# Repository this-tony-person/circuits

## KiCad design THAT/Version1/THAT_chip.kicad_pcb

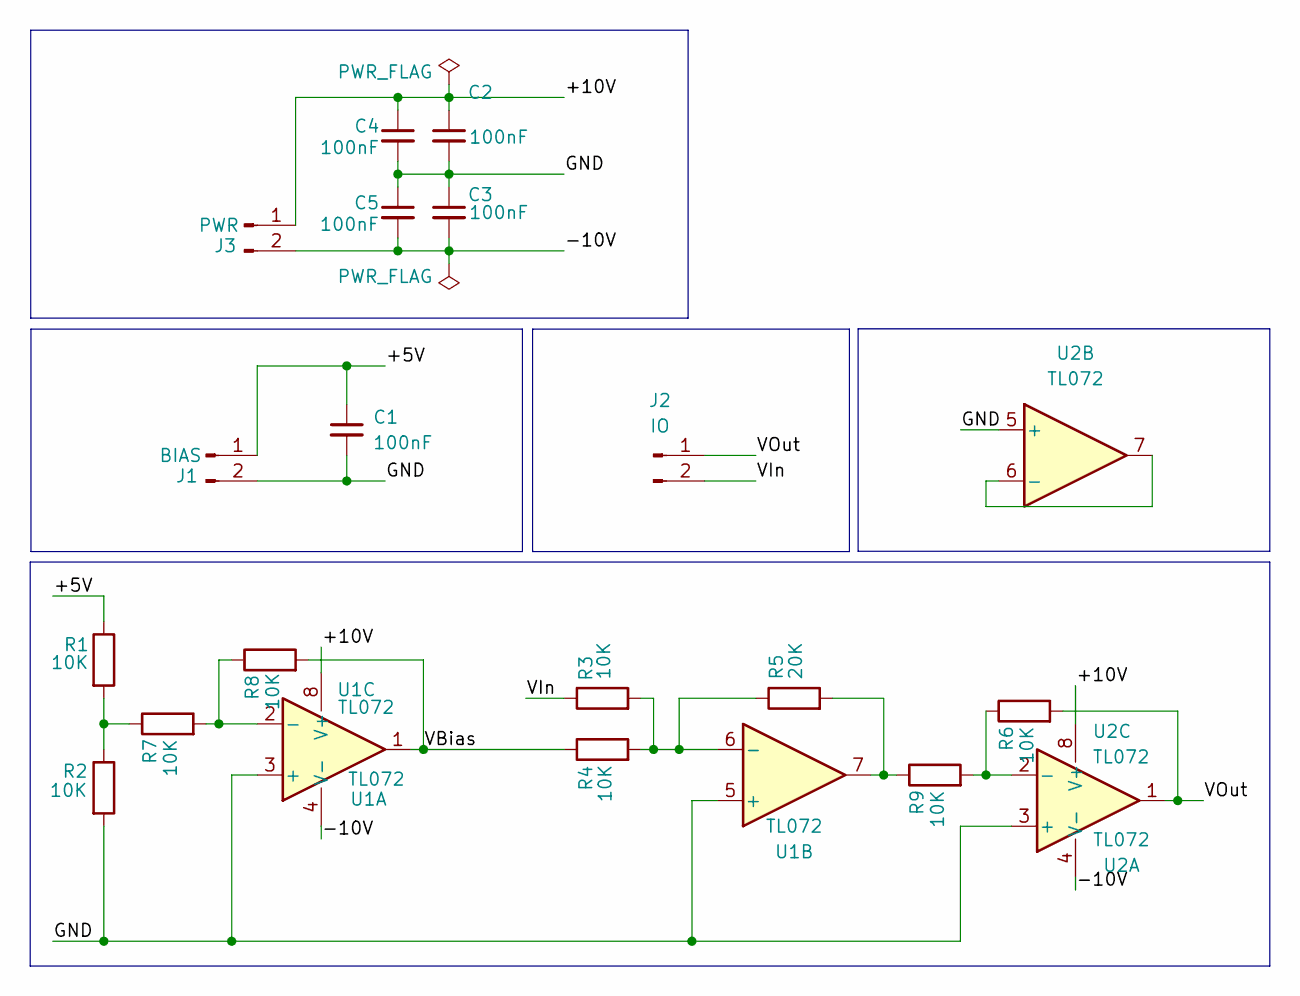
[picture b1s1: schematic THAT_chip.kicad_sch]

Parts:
C1, C2, C3, C4, C5: 100nF; C_Disc_D5.1mm_W3.2mm_P5.00mm
J1: BIAS; PinHeader_1x02_P2.54mm_Vertical
J2: IO; PinHeader_1x02_P2.54mm_Vertical
J3: PWR; PinHeader_1x02_P2.54mm_Vertical
R1, R2, R3, R4, R6, R7, R8, R9: 10K; R_Axial_DIN0207_L6.3mm_D2.5mm_P7.62mm_Horizontal
R5: 20K; R_Axial_DIN0207_L6.3mm_D2.5mm_P7.62mm_Horizontal
U1, U2: TL072

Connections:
/+5V: C1.1, J1.1, R1.1
/+10V: C2.1, C4.1, J3.1, U1.8 (V+), U2.8 (V+)
/-10V: C3.2, C5.2, J3.2, U1.4 (V-), U2.4 (V-)
/GND: C1.2, C2.2, C3.1, C4.2, C5.1, J1.2, R2.2, U1.3 (+), U1.5 (+), U2.3 (+), U2.5 (+)
/VBias: R4.1, R8.2, U1.1
/VIn: J2.2, R3.1
/VOut: J2.1, R6.2, U2.1
unnamed: R1.2, R2.1, R7.1
unnamed: R5.2, R9.1, U1.7
unnamed: R7.2, R8.1, U1.2 (-)
unnamed: R3.2, R4.2, R5.1, U1.6 (-)
unnamed: R6.1, R9.2, U2.2 (-)
unnamed: U2.6 (-), U2.7

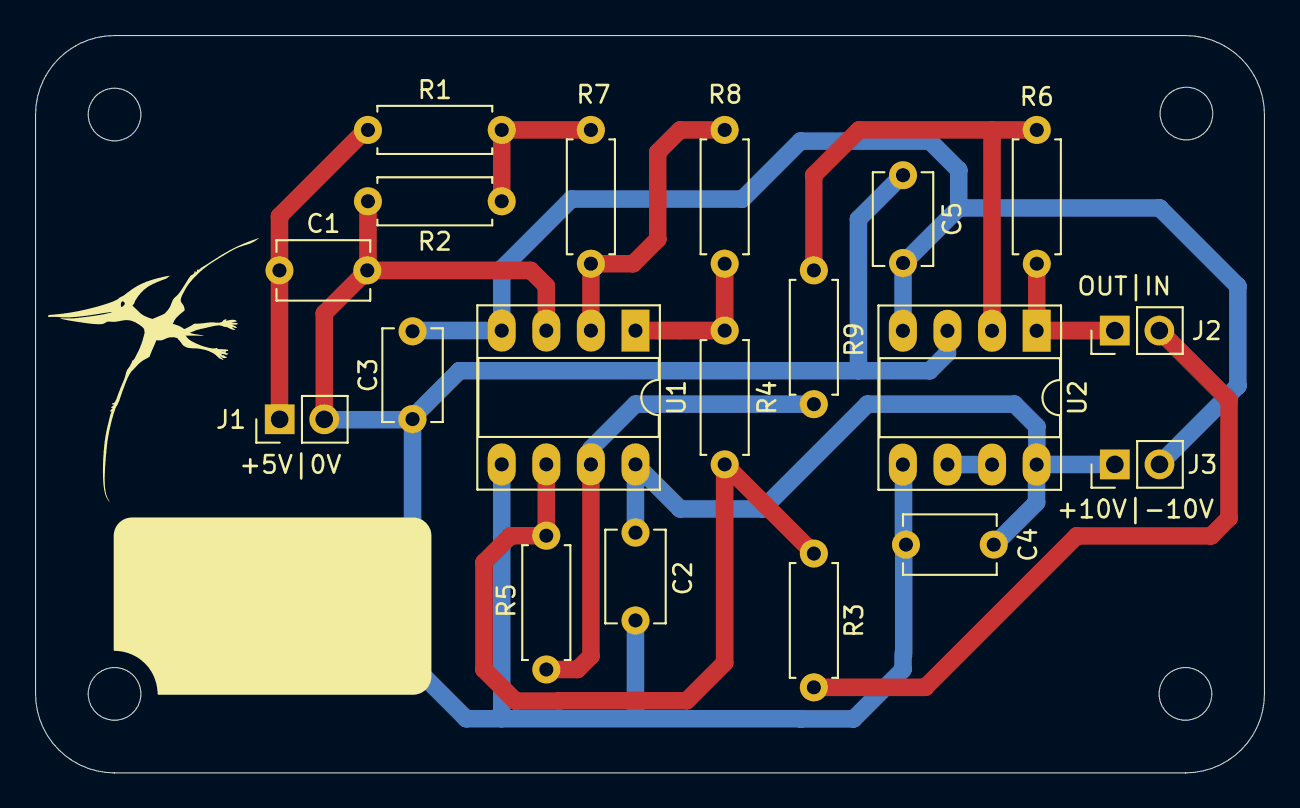
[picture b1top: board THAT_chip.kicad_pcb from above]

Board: 2 copper layers, 70.0 x 42.0 mm, 19 parts (0 on the bottom side), 13 nets.

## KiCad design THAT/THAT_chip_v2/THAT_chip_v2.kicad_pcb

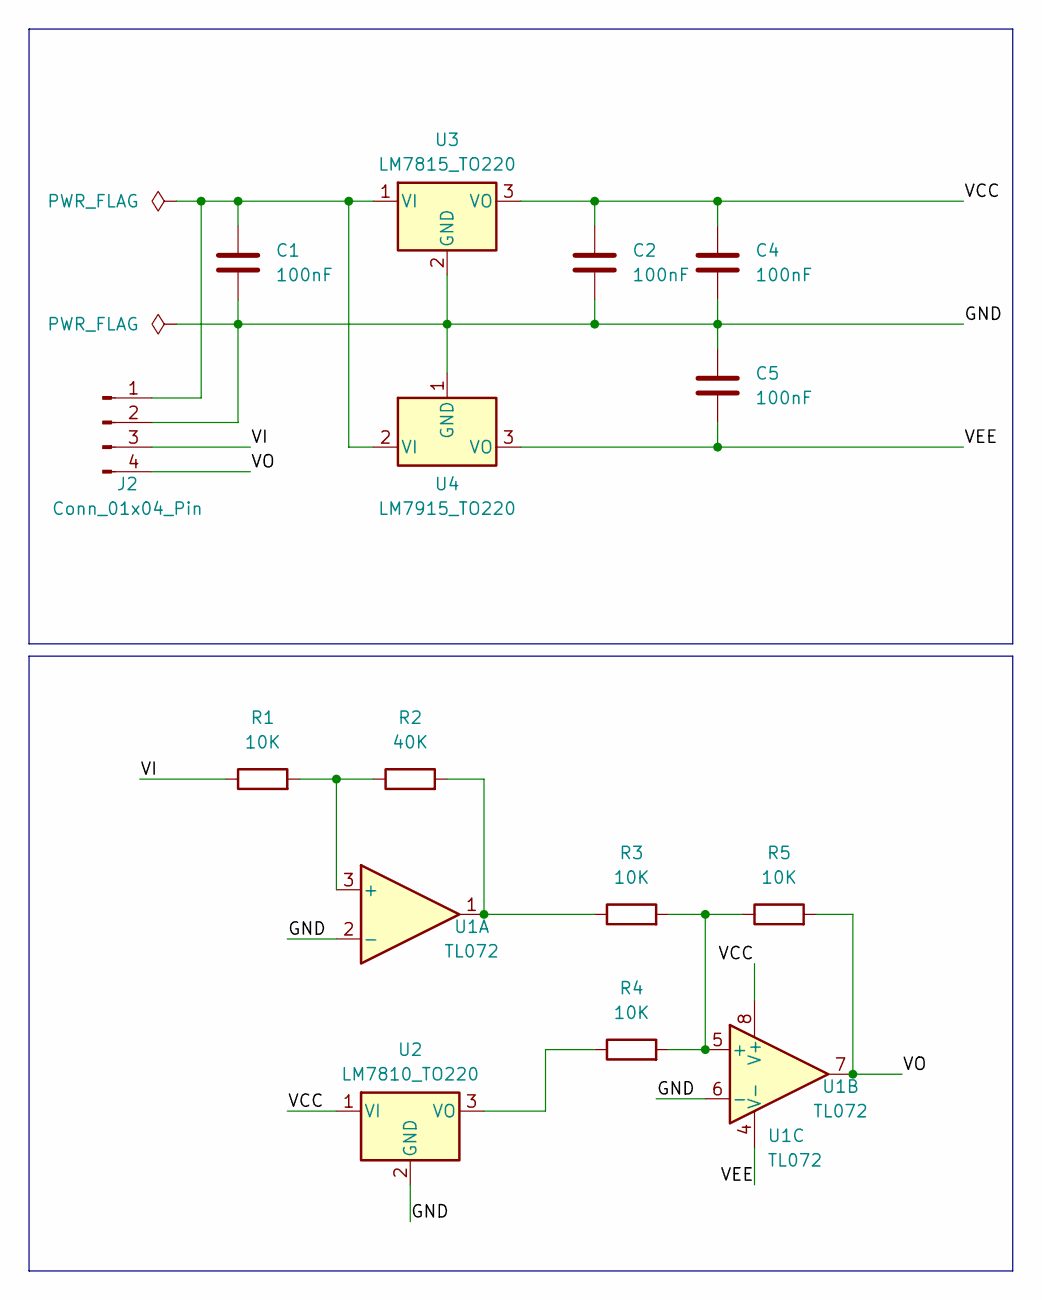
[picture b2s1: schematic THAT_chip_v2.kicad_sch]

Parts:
C1, C2, C4, C5: 100nF; C_Disc_D5.1mm_W3.2mm_P5.00mm
J2: Conn_01x04_Pin; PinHeader_1x04_P2.54mm_Vertical
R1, R3, R4, R5: 10K; R_Axial_DIN0207_L6.3mm_D2.5mm_P7.62mm_Horizontal
R2: 40K; R_Axial_DIN0207_L6.3mm_D2.5mm_P7.62mm_Horizontal
U1: TL072; DIP-8_W7.62mm_Socket_LongPads
U2: LM7810_TO220; TO-220-3_Vertical
U3: LM7815_TO220; TO-220-3_Vertical
U4: LM7915_TO220; TO-220-3_Vertical

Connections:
/GND: C1.2, C2.2, C4.2, C5.1, J2.2, U1.2 (-), U1.6 (-), U2.2 (GND), U3.2 (GND), U4.1 (GND)
/VCC: C2.1, C4.1, U1.8 (V+), U2.1 (VI), U3.3 (VO)
/VEE: C5.2, U1.4 (V-), U4.3 (VO)
/VI: J2.3, R1.1
/VO: J2.4, R5.2, U1.7
unnamed: C1.1, J2.1, U3.1 (VI), U4.2 (VI)
unnamed: R2.2, R3.1, U1.1
unnamed: R1.2, R2.1, U1.3 (+)
unnamed: R3.2, R4.2, R5.1, U1.5 (+)
unnamed: R4.1, U2.3 (VO)

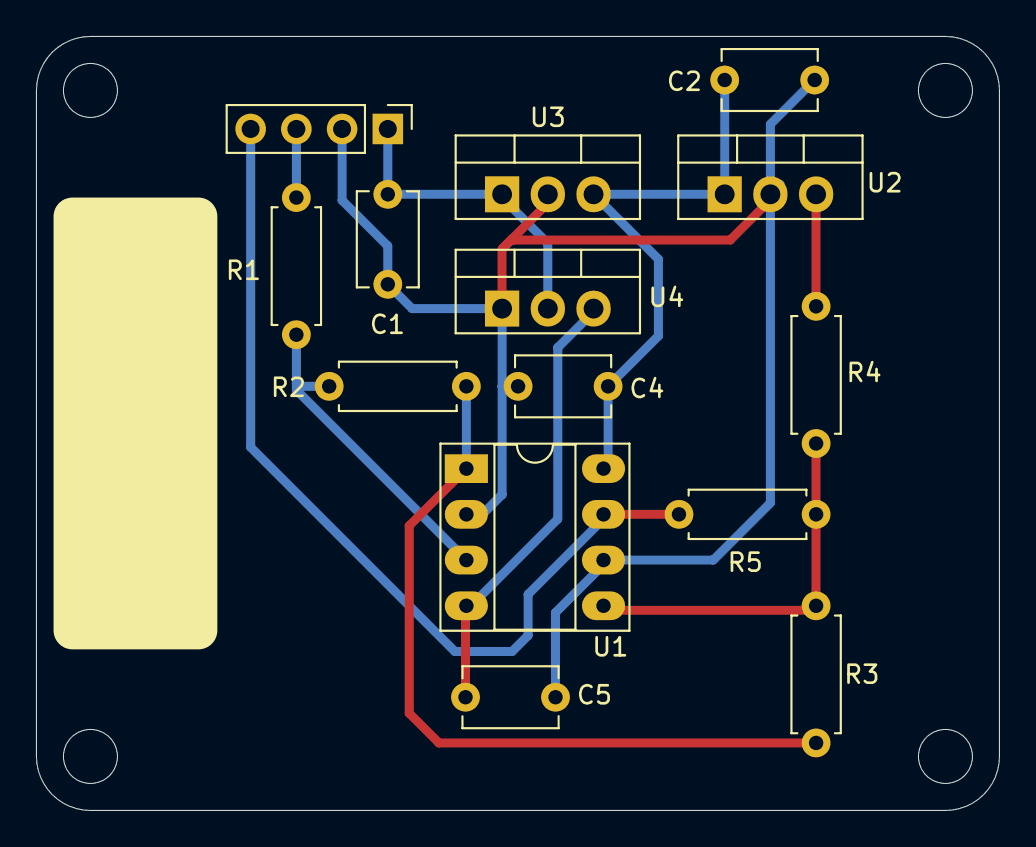
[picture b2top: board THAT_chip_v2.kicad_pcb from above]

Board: 2 copper layers, 53.5 x 43.0 mm, 14 parts (0 on the bottom side), 10 nets.

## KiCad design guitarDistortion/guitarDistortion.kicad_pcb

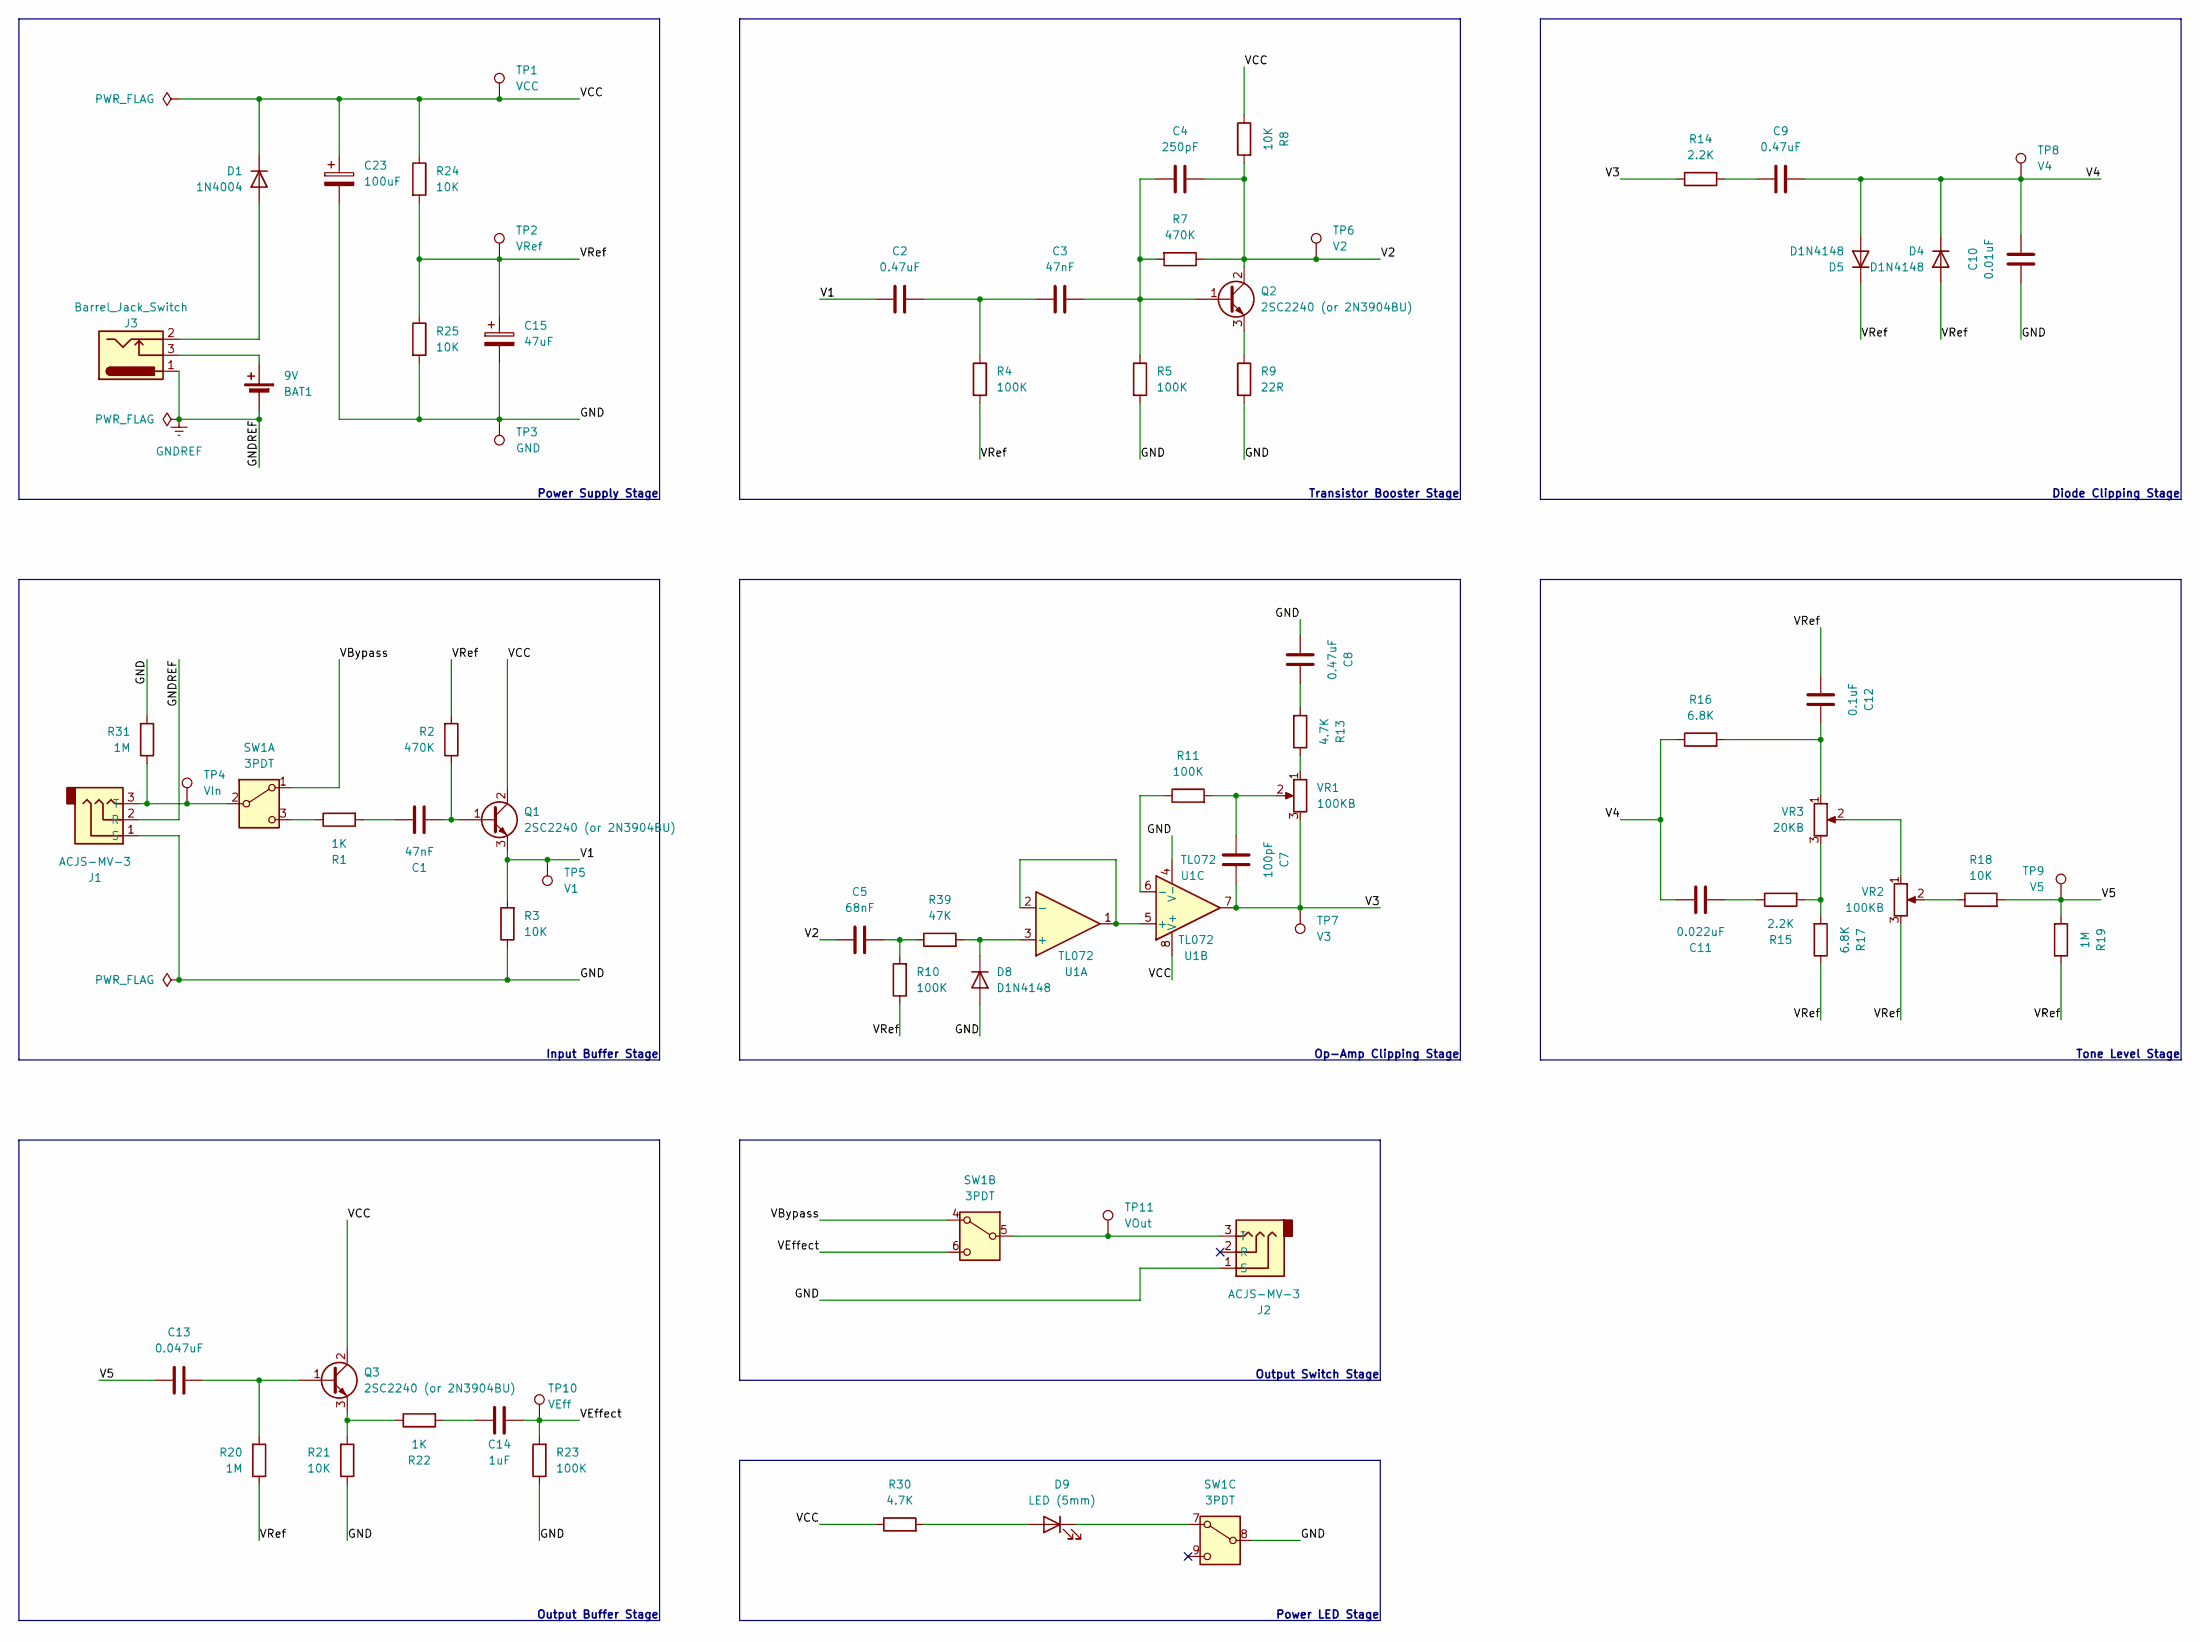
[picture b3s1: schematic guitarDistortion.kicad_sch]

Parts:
BAT1: 9V; JST_PH_B2B-PH-K_1x02_P2.00mm_Vertical
C1, C3: 47nF; C_Disc_D5.1mm_W3.2mm_P2.54mm
C2, C8, C9: 0.47uF; C_Disc_D5.1mm_W3.2mm_P2.54mm
C4: 250pF; C_Disc_D5.1mm_W3.2mm_P2.54mm
C5: 68nF; C_Disc_D5.1mm_W3.2mm_P2.54mm
C7: 100pF; C_Disc_D5.1mm_W3.2mm_P2.54mm
C10: 0.01uF; C_Disc_D5.1mm_W3.2mm_P2.54mm
C11: 0.022uF; C_Disc_D5.1mm_W3.2mm_P2.54mm
C12: 0.1uF; C_Disc_D5.1mm_W3.2mm_P2.54mm
C13: 0.047uF; C_Disc_D5.1mm_W3.2mm_P2.54mm
C14: 1uF; C_Disc_D5.1mm_W3.2mm_P2.54mm
C15: 47uF; C_Radial_D5.0mm_H11.0mm_P2.00mm
C23: 100uF; C_Radial_D5.0mm_H11.0mm_P2.00mm
D1: 1N4004; D_DO-41_SOD81_P7.62mm_Horizontal
D4, D5, D8: D1N4148; D_DO-35_SOD27_P7.62mm_Horizontal
D9: LED (5mm); JST_PH_S2B-PH-K_1x02_P2.00mm_Horizontal
J1, J2: ACJS-MV-3; JST_PH_S3B-PH-K_1x03_P2.00mm_Horizontal
J3: Barrel_Jack_Switch; JST_PH_S3B-PH-K_1x03_P2.00mm_Horizontal
Q1, Q2, Q3: 2SC2240 (or 2N3904BU); TO-92L_Inline
R1, R22: 1K; R_Axial_DIN0207_L6.3mm_D2.5mm_P7.62mm_Horizontal
R2, R7: 470K; R_Axial_DIN0207_L6.3mm_D2.5mm_P7.62mm_Horizontal
R3, R8, R18, R21, R24, R25: 10K; R_Axial_DIN0207_L6.3mm_D2.5mm_P7.62mm_Horizontal
R4, R5, R10, R11, R23: 100K; R_Axial_DIN0207_L6.3mm_D2.5mm_P7.62mm_Horizontal
R9: 22R; R_Axial_DIN0207_L6.3mm_D2.5mm_P7.62mm_Horizontal
R13, R30: 4.7K; R_Axial_DIN0207_L6.3mm_D2.5mm_P7.62mm_Horizontal
R14, R15: 2.2K; R_Axial_DIN0207_L6.3mm_D2.5mm_P7.62mm_Horizontal
R16, R17: 6.8K; R_Axial_DIN0207_L6.3mm_D2.5mm_P7.62mm_Horizontal
R19, R20, R31: 1M; R_Axial_DIN0207_L6.3mm_D2.5mm_P7.62mm_Horizontal
R39: 47K; R_Axial_DIN0207_L6.3mm_D2.5mm_P7.62mm_Horizontal
SW1: 3PDT; JST_PH_B9B-PH-K_1x09_P2.00mm_Vertical
TP1: VCC; TestPoint_THTPad_1.5x1.5mm_Drill0.7mm
TP2: VRef; TestPoint_THTPad_1.5x1.5mm_Drill0.7mm
TP3: GND; TestPoint_THTPad_1.5x1.5mm_Drill0.7mm
TP4: VIn; TestPoint_THTPad_1.5x1.5mm_Drill0.7mm
TP5: V1; TestPoint_THTPad_1.5x1.5mm_Drill0.7mm
TP6: V2; TestPoint_THTPad_1.5x1.5mm_Drill0.7mm
TP7: V3; TestPoint_THTPad_1.5x1.5mm_Drill0.7mm
TP8: V4; TestPoint_THTPad_1.5x1.5mm_Drill0.7mm
TP9: V5; TestPoint_THTPad_1.5x1.5mm_Drill0.7mm
TP10: VEff; TestPoint_THTPad_1.5x1.5mm_Drill0.7mm
TP11: VOut; TestPoint_THTPad_1.5x1.5mm_Drill0.7mm
U1: TL072; DIP-8_W7.62mm_Socket_LongPads
VR1, VR2: 100KB; JST_PH_S3B-PH-K_1x03_P2.00mm_Horizontal
VR3: 20KB; JST_PH_S3B-PH-K_1x03_P2.00mm_Horizontal

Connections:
/GND: C8.2, C10.1, C15.2, C23.2, D8.2 (A), J1.1 (S), J2.1 (S), R3.1, R5.2, R9.2, R21.1, R23.1, R25.2, R31.2, SW1.8, TP3.1, U1.4 (V-)
/V1: C2.2, Q1.3 (E), R3.2, TP5.1
/V2: C4.2, C5.1, Q2.2 (C), R7.1, R8.2, TP6.1
/V3: C7.1, R14.1, TP7.1, U1.7, VR1.3
/V4: C9.1, C10.2, C11.2, D4.1 (K), D5.2 (A), R16.1, TP8.1
/V5: C13.1, R18.2, R19.2, TP9.1
/VBypass: SW1.1, SW1.4
/VCC: C23.1, D1.1 (K), Q1.2 (C), Q3.2 (C), R8.1, R24.1, R30.1, TP1.1, U1.8 (V+)
/VEffect: C14.2, R23.2, SW1.6, TP10.1
/VRef: C12.1, C15.1, D4.2 (A), D5.1 (K), R2.2, R4.2, R10.1, R17.1, R19.1, R20.1, R24.2, R25.1, TP2.1, VR2.3
GNDREF: BAT1.2 (-), J1.2 (R), J3.1
unnamed: C1.1, R1.2
unnamed: C2.1, C3.2, R4.1
unnamed: C5.2, R10.2, R39.1
unnamed: C7.2, R11.2, VR1.2
unnamed: C8.1, R13.2
unnamed: C9.2, R14.2
unnamed: C11.1, R15.1
unnamed: C12.2, R16.2, VR3.1
unnamed: C14.1, R22.2
unnamed: D1.2 (A), J3.2
unnamed: D8.1 (K), R39.2, U1.3 (+)
unnamed: D9.2 (A), R30.2
unnamed: D9.1 (K), SW1.7
unnamed: J1.3 (T), R31.1, SW1.2, TP4.1
unnamed: J2.3 (T), SW1.5, TP11.1
unnamed: BAT1.1 (+), J3.3
unnamed: C1.2, Q1.1 (B), R2.1
unnamed: C3.1, C4.1, Q2.1 (B), R5.1, R7.2
unnamed: Q2.3 (E), R9.1
unnamed: C13.2, Q3.1 (B), R20.2
unnamed: Q3.3 (E), R21.2, R22.1
unnamed: R1.1, SW1.3
unnamed: R13.1, VR1.1
unnamed: R15.2, R17.2, VR3.3
unnamed: R18.1, VR2.2
unnamed: U1.1, U1.2 (-), U1.5 (+)
unnamed: R11.1, U1.6 (-)
unnamed: VR2.1, VR3.2

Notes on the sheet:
Output Switch Stage
Input Buffer Stage
Power LED Stage
Diode Clipping Stage
Tone Level Stage
Op-Amp Clipping Stage
Power Supply Stage
Transistor Booster Stage
Output Buffer Stage

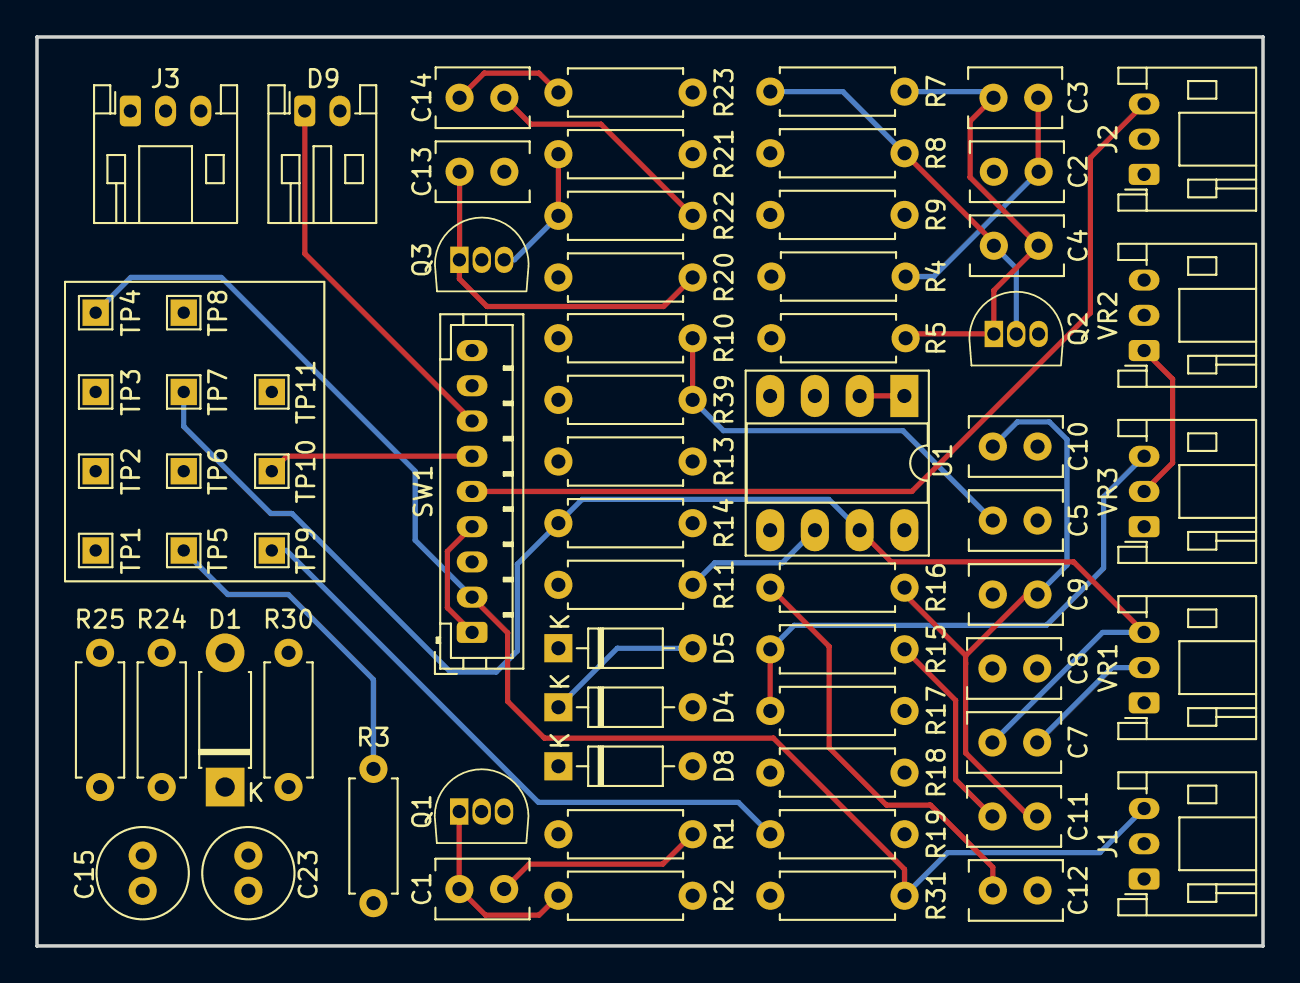
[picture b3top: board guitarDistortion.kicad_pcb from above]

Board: 4 copper layers, 69.6 x 51.6 mm, 68 parts (0 on the bottom side), 38 nets.

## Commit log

2025-06-17 Boss DS1 distortion kicad files
2025-06-17 Kicad files for interfacing circuit between THAT analog and digital computer
2025-06-17 Kicad files in case they are needed
2025-06-17 Digital effects pedal kicad files
2025-06-18 Updates to digital pedal circuti
